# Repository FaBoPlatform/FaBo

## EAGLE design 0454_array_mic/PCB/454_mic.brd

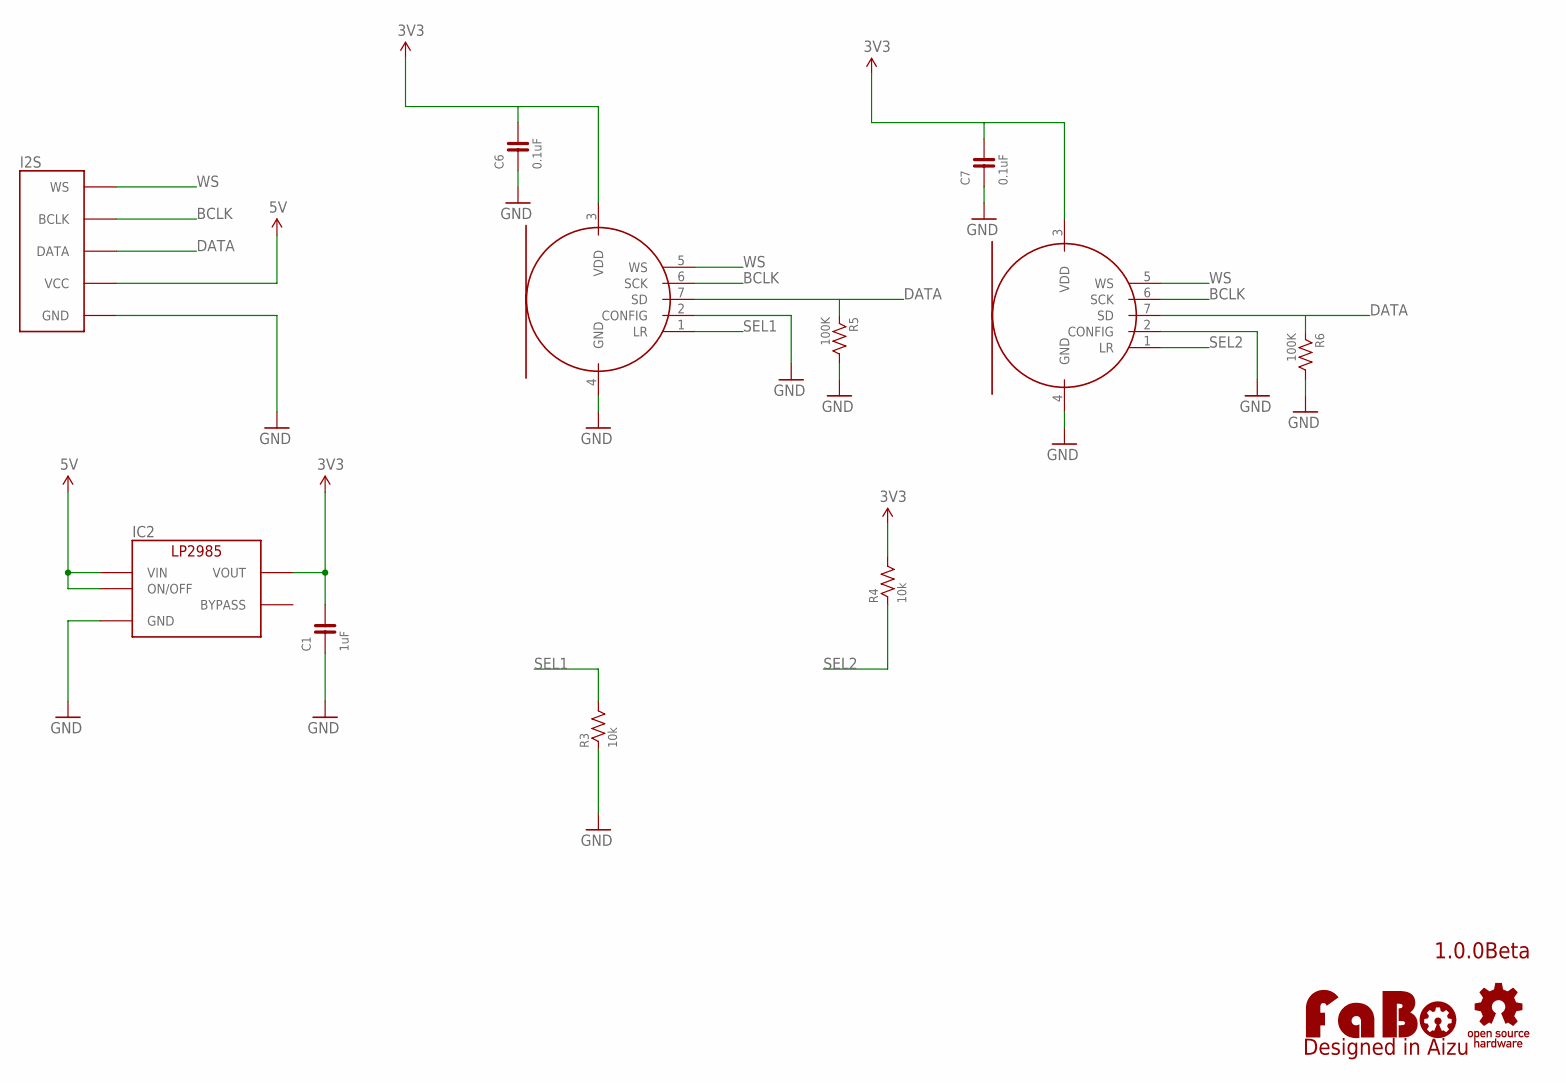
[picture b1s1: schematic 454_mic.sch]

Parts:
C1: 1uF; 0603
C6, C7: 0.1uF; 0603
I2S: FABO_BRICK_I2STOP; FABO_BRICK_I2S_B05B-PARK-1
IC2: LP2985-33DBV; SOT-23-5
LOGO1: LOGO_FABO-M_BOTTOM; LOGO_FABO_M_BOTTOM
MIC_LEFT: TDK-ICS43432
MIC_RIGHT: TDK-ICS43432
R3, R4: 10k; 0603
R5, R6: 100K; 0603
U$2: LOGO_OSHW-M; LOGO_OSHW_M

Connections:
3V3: C1.2, C6.2, C7.2, IC2.5 (VOUT), MIC_LEFT.3 (VDD), MIC_RIGHT.3 (VDD), R4.2
5V: I2S.VCC, IC2.1 (VIN), IC2.3 (ON/OFF)
BCLK: I2S.BCLK, MIC_LEFT.6 (SCK), MIC_RIGHT.6 (SCK)
DATA: I2S.DATA, MIC_LEFT.7 (SD), MIC_RIGHT.7 (SD), R5.1, R6.1
GND: C1.1, C6.1, C7.1, I2S.GND, IC2.2 (GND), MIC_LEFT.2 (CONFIG), MIC_LEFT.4 (GND), MIC_RIGHT.2 (CONFIG), MIC_RIGHT.4 (GND), R3.1, R5.2, R6.2
SEL1: MIC_LEFT.1 (LR), R3.2
SEL2: MIC_RIGHT.1 (LR), R4.1
WS: I2S.WS, MIC_LEFT.5 (WS), MIC_RIGHT.5 (WS)

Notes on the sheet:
1.0.0Beta

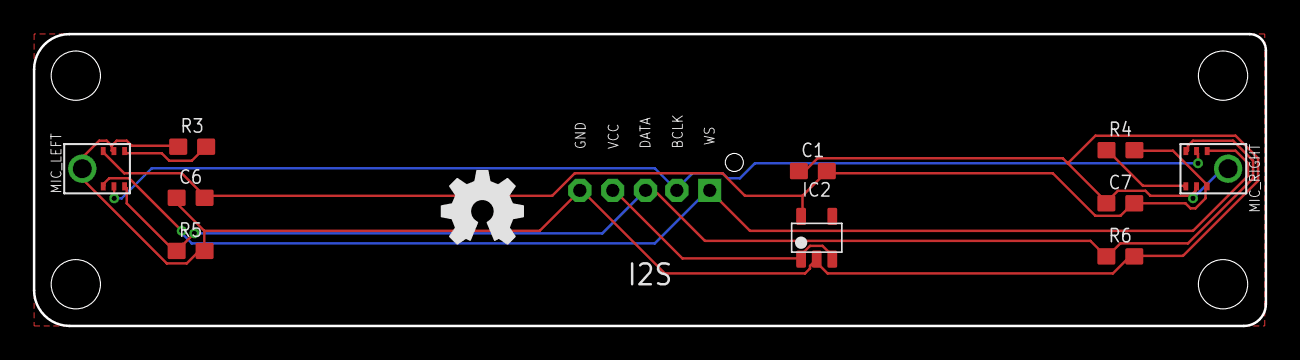
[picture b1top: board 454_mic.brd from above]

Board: 2 copper layers, 75.0 x 17.8 mm, 13 parts (0 on the bottom side), 8 nets.

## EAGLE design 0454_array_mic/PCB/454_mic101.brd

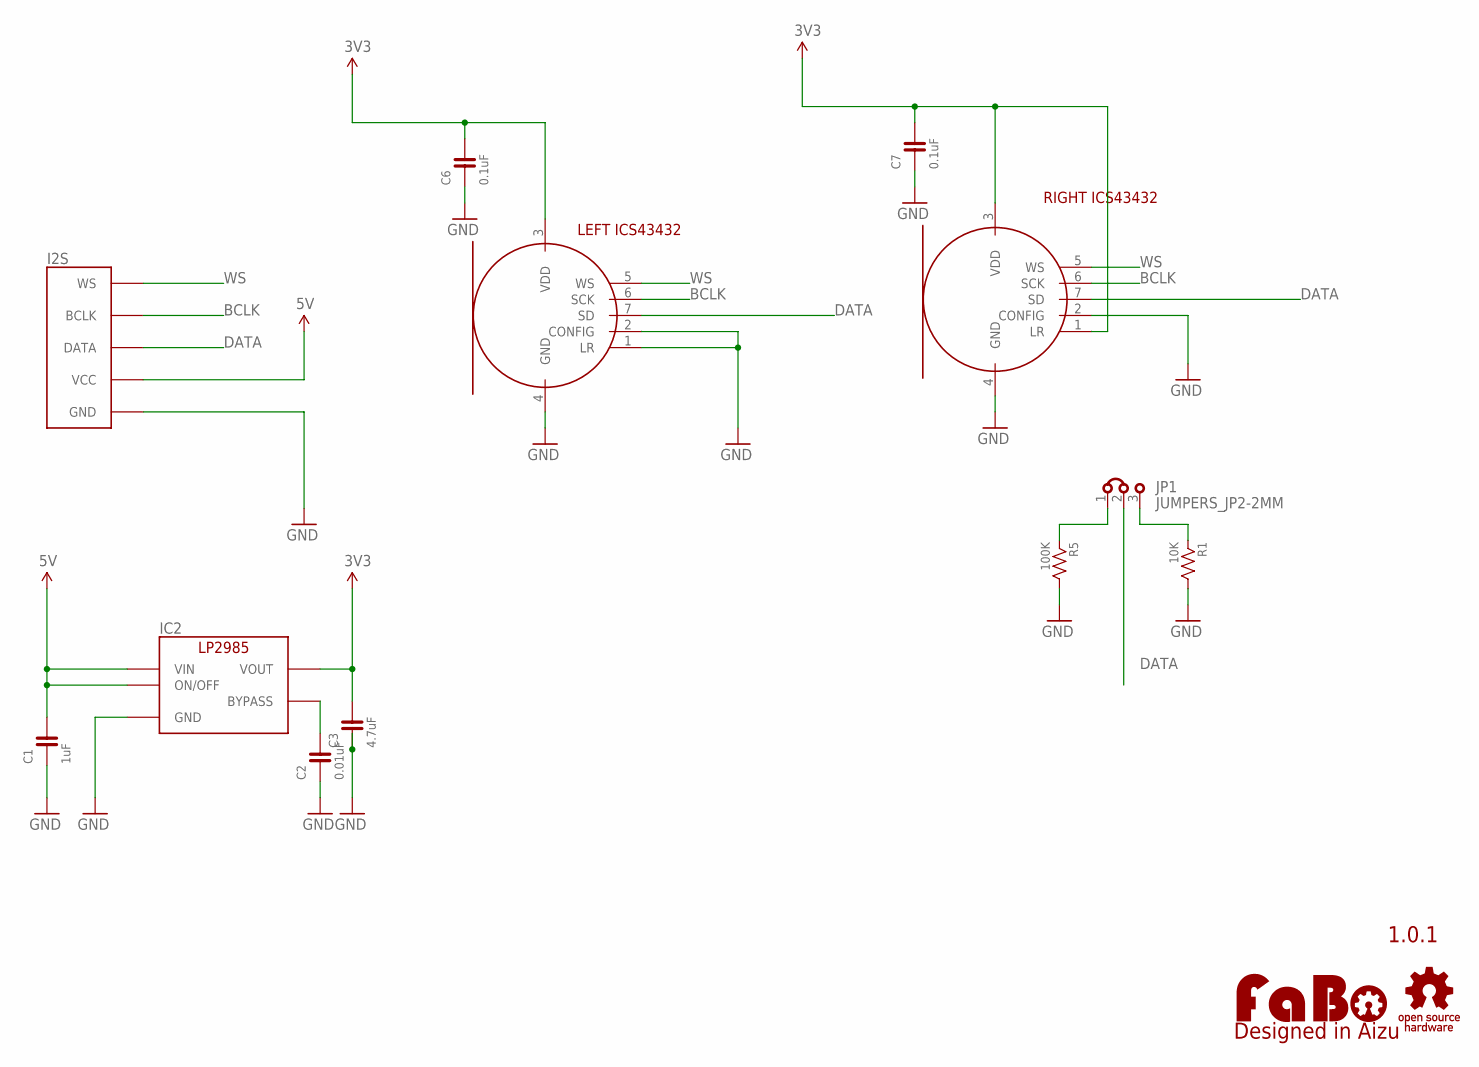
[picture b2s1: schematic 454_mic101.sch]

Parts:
C1: 1uF; 0603
C2: 0.01uF; 0603
C3: 4.7uF; 0603
C6, C7: 0.1uF; 0603
I2S: FABO_BRICK_I2STOP; FABO_BRICK_I2S_B05B-PARK-1
IC2: LP2985-33DBV; SOT-23-5
JP1: JUMPERS_JP2-2MM
LOGO1: LOGO_FABO-M_BOTTOM; LOGO_FABO_M_BOTTOM
MIC_LEFT: TDK-ICS43432
MIC_RIGHT: TDK-ICS43432
R1: 10K; 0603
R5: 100K; 0603
U$2: LOGO_OSHW-M; LOGO_OSHW_M

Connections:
3V3: C3.2, C6.2, C7.2, IC2.5 (VOUT), MIC_LEFT.3 (VDD), MIC_RIGHT.1 (LR), MIC_RIGHT.3 (VDD)
5V: C1.2, I2S.VCC, IC2.1 (VIN), IC2.3 (ON/OFF)
BCLK: I2S.BCLK, MIC_LEFT.6 (SCK), MIC_RIGHT.6 (SCK)
DATA: I2S.DATA, JP1.2, MIC_LEFT.7 (SD), MIC_RIGHT.7 (SD)
GND: C1.1, C2.1, C3.1, C6.1, C7.1, I2S.GND, IC2.2 (GND), MIC_LEFT.1 (LR), MIC_LEFT.2 (CONFIG), MIC_LEFT.4 (GND), MIC_RIGHT.2 (CONFIG), MIC_RIGHT.4 (GND), R1.2, R5.2
unnamed: C2.2, IC2.4 (BYPASS)
unnamed: JP1.1, R5.1
unnamed: JP1.3, R1.1
WS: I2S.WS, MIC_LEFT.5 (WS), MIC_RIGHT.5 (WS)

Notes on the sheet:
1.0.1
LEFT ICS43432
RIGHT ICS43432

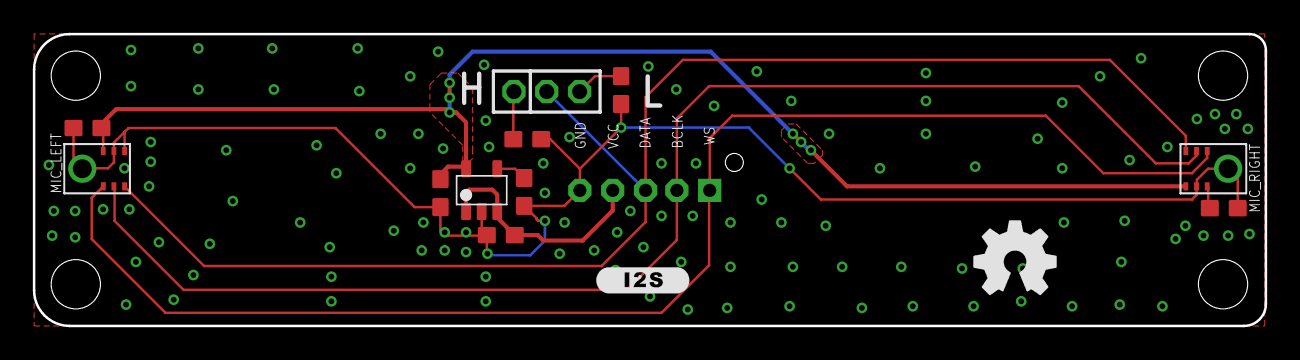
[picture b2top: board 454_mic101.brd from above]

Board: 2 copper layers, 75.0 x 17.8 mm, 14 parts (0 on the bottom side), 9 nets.

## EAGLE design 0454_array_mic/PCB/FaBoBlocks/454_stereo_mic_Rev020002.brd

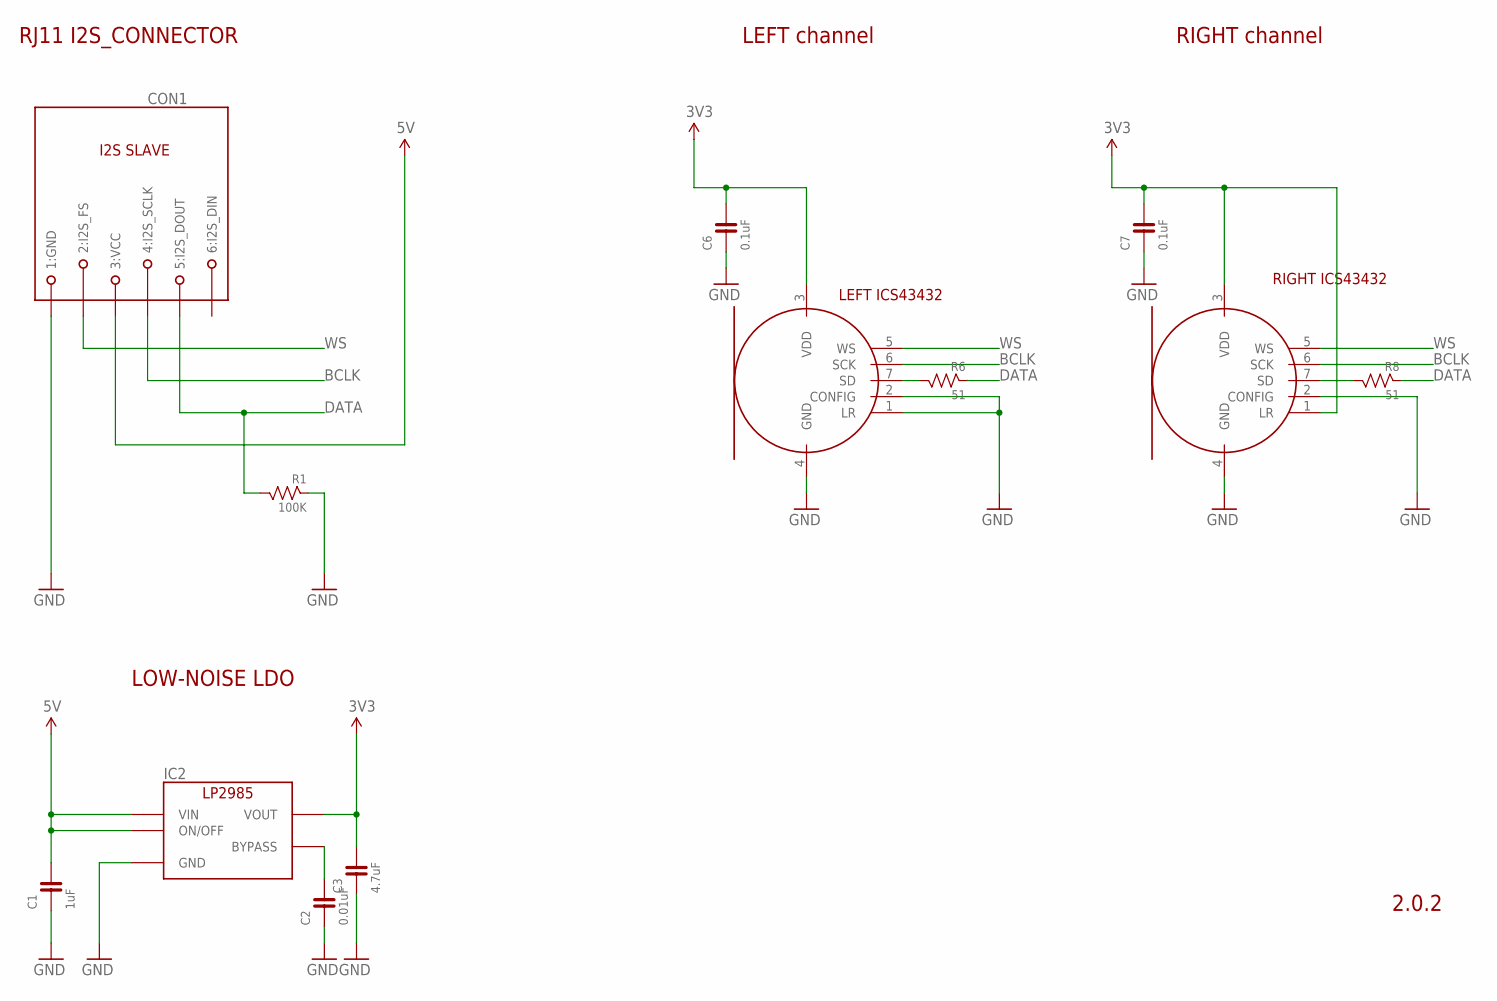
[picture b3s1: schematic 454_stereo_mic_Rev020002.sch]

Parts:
C1: 1uF; 0603
C2: 0.01uF; 0603
C3: 4.7uF; 0603
C6, C7: 0.1uF; 0603
CON1: MODULAR-JACK-6P-RJ11_I2S_SLAVE; 7002-6PXC-X
IC2: LP2985-33DBV; SOT-23-5
MIC_LEFT: TDK-ICS43432
MIC_RIGHT: TDK-ICS43432
R1: 100K; 0603
R6, R8: 51; 0603

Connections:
3V3: C3.2, C6.2, C7.2, IC2.5 (VOUT), MIC_LEFT.3 (VDD), MIC_RIGHT.1 (LR), MIC_RIGHT.3 (VDD)
5V: C1.2, CON1.3 (3:VCC), IC2.1 (VIN), IC2.3 (ON/OFF)
BCLK: CON1.4 (4:I2S_SCLK), MIC_LEFT.6 (SCK), MIC_RIGHT.6 (SCK)
DATA: CON1.5 (5:I2S_DOUT), R1.2, R6.1, R8.1
GND: C1.1, C2.1, C3.1, C6.1, C7.1, CON1.1 (1:GND), IC2.2 (GND), MIC_LEFT.1 (LR), MIC_LEFT.2 (CONFIG), MIC_LEFT.4 (GND), MIC_RIGHT.2 (CONFIG), MIC_RIGHT.4 (GND), R1.1
unnamed: C2.2, IC2.4 (BYPASS)
unnamed: MIC_LEFT.7 (SD), R6.2
unnamed: MIC_RIGHT.7 (SD), R8.2
WS: CON1.2 (2:I2S_FS), MIC_LEFT.5 (WS), MIC_RIGHT.5 (WS)

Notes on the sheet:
2.0.2
LEFT ICS43432
RIGHT ICS43432
LEFT channel
RIGHT channel
RJ11 I2S_CONNECTOR
LOW-NOISE LDO

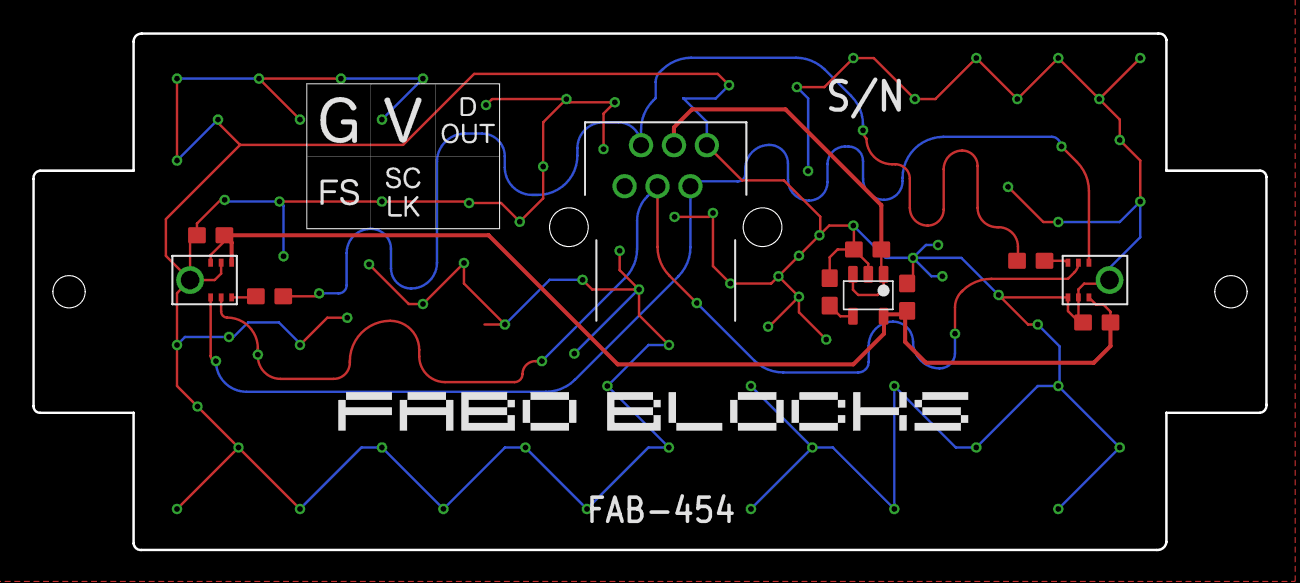
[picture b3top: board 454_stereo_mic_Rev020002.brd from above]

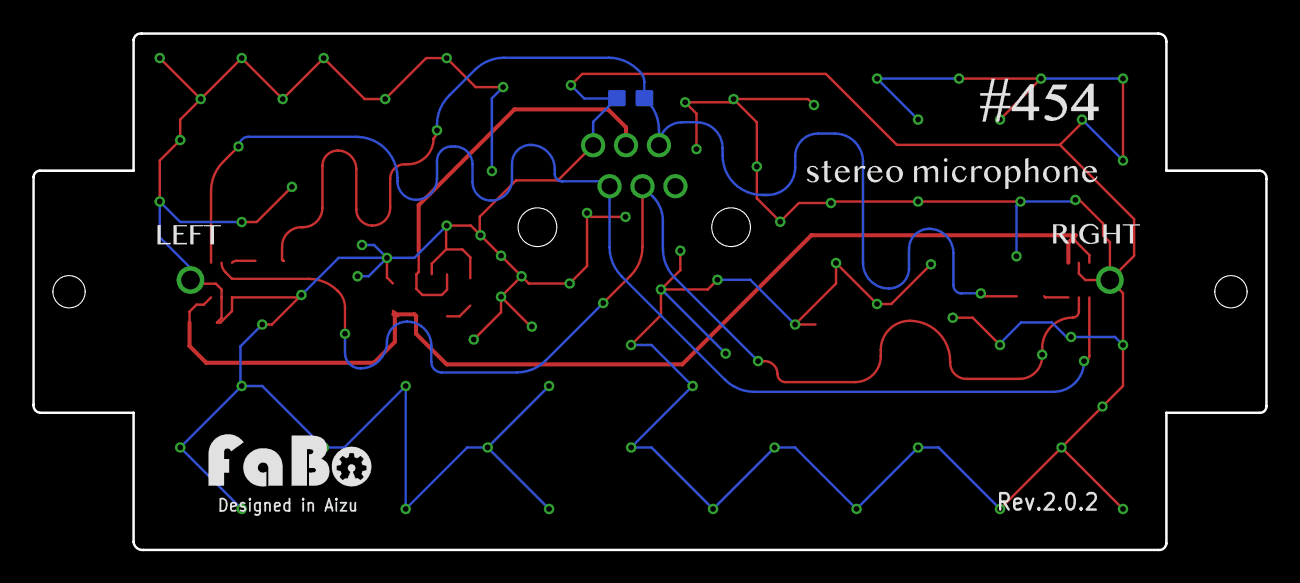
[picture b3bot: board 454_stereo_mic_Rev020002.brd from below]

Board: 2 copper layers, 76.4 x 32.0 mm, 15 parts (2 on the bottom side), 9 nets.

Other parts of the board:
U$2, U$3: 4-1BLOCK
U$4: LOGO_FABO_M

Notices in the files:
parts and their libraries:
FaBo-Capacitor: Released under the Creative Commons Attribution-ShareAlike 4.0 License
https://creativecommons.org/licenses/by-sa/4.0
FaBo-etc: Released under the Creative Commons
